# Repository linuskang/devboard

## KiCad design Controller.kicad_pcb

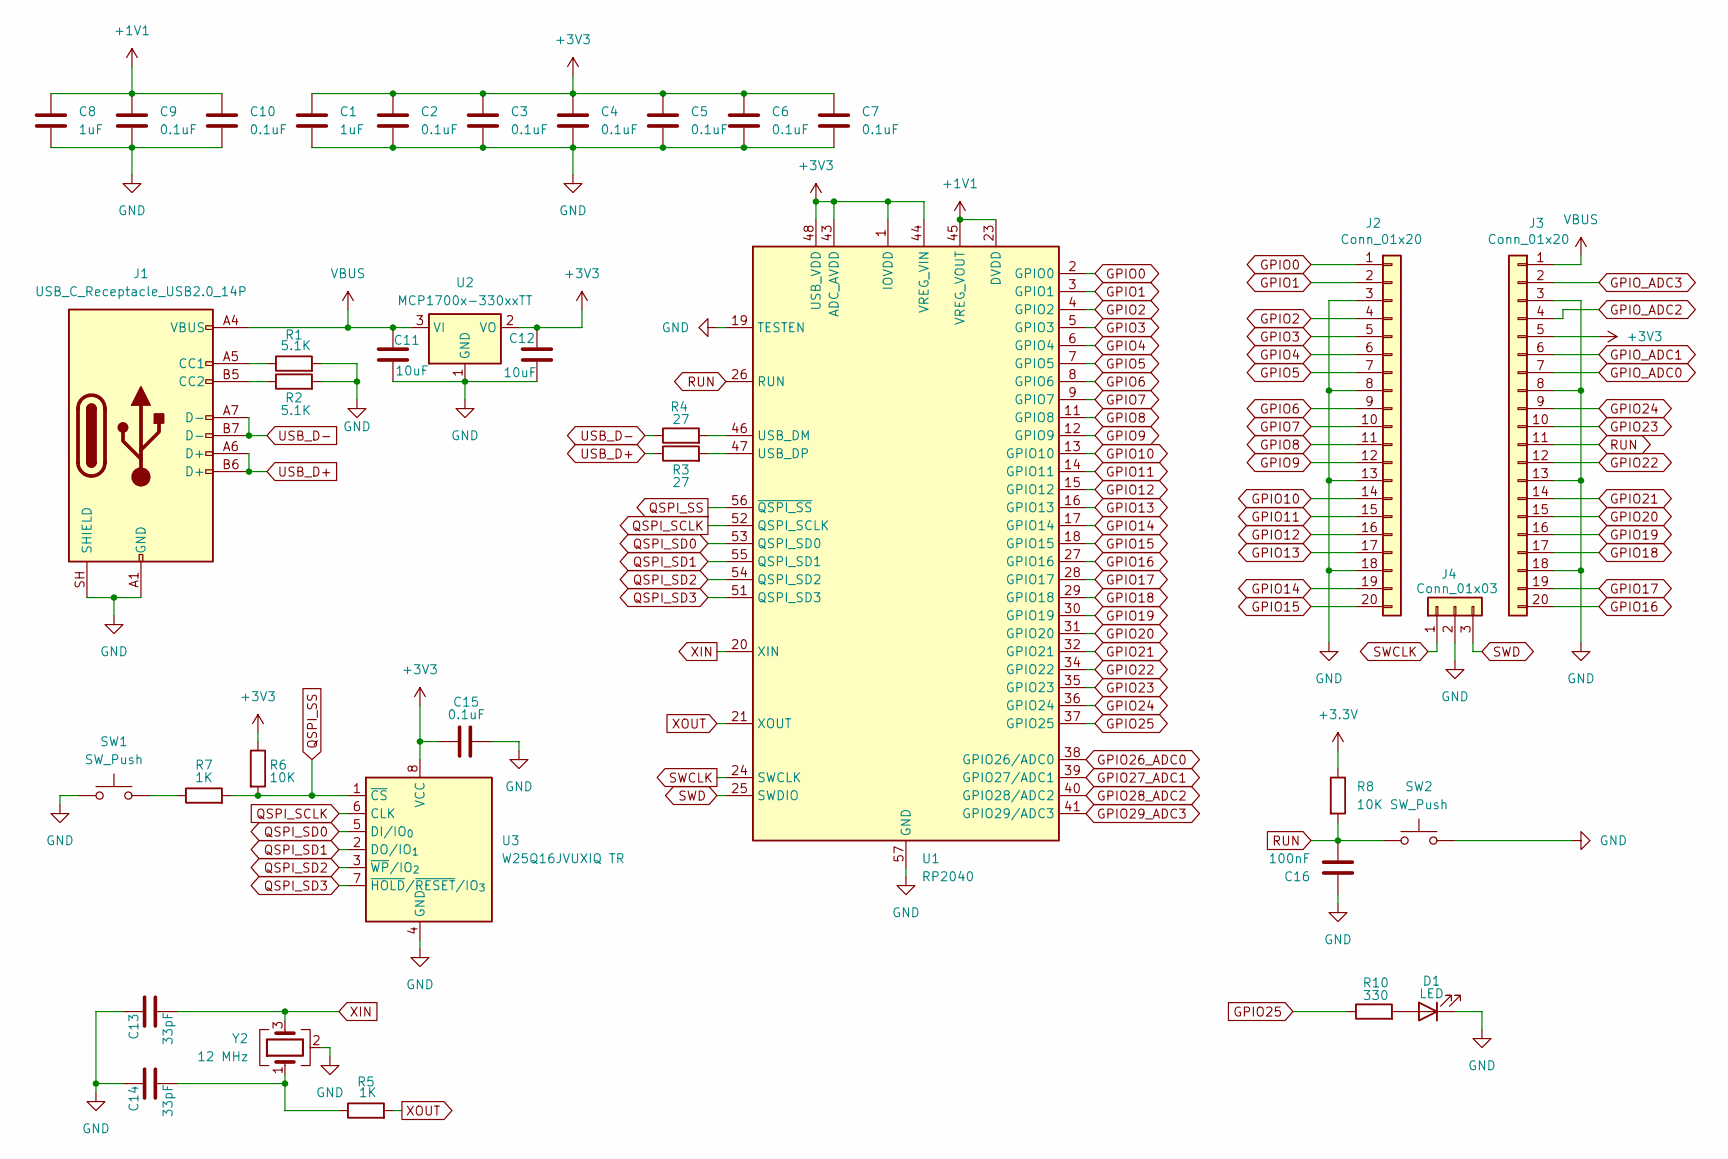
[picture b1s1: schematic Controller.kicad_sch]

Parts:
C1, C8: 1uF; C_0402_1005Metric
C2, C3, C4, C5, C6, C7, C9, C10, C15: 0.1uF; C_0402_1005Metric
C11, C12: 10uF; C_0402_1005Metric
C13, C14: 33pF; C_0402_1005Metric
C16: 100nF; C_0402_1005Metric
D1: LED; LED_0805_2012Metric_Pad1.15x1.40mm_HandSolder
J1: USB_C_Receptacle_USB2.0_14P; USB_C_Receptacle_HRO_TYPE-C-31-M-12
J2, J3: Conn_01x20; PinHeader_1x20_P2.54mm_Vertical
J4: Conn_01x03; PinHeader_1x03_P2.54mm_Vertical
R1, R2: 5.1K; R_0402_1005Metric
R3, R4: 27; R_0402_1005Metric
R5, R7: 1K; R_0402_1005Metric
R6, R8: 10K; R_0402_1005Metric
R10: 330; R_0402_1005Metric
SW1, SW2: SW_Push; SW_Push_SPST_NO_Alps_SKRK
U1: RP2040; QFN-56-1EP_7x7mm_P0.4mm_EP3.2x3.2mm
U2: MCP1700x-330xxTT; SOT-23
U3: W25Q16JVUXIQ TR; Winbond_USON-8-1EP_3x2mm_P0.5mm_EP0.2x1.6mm
Y2: 12 MHz; Crystal_SMD_3225-4Pin_3.2x2.5mm

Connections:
+1V1: C8.1, C9.1, C10.1, U1.23 (DVDD), U1.45 (VREG_VOUT), U1.50 (DVDD)
+3.3V: R8.1
+3V3: C1.1, C2.1, C3.1, C4.1, C5.1, C6.1, C7.1, C12.1, C15.2, J3.5, R6.1, U1.1 (IOVDD), U1.10 (IOVDD), U1.22 (IOVDD), U1.33 (IOVDD), U1.42 (IOVDD), U1.43 (ADC_AVDD), U1.44 (VREG_VIN), U1.48 (USB_VDD), U1.49 (IOVDD), U2.2 (VO), U3.8 (VCC)
GND: C1.2, C2.2, C3.2, C4.2, C5.2, C6.2, C7.2, C8.2, C9.2, C10.2, C11.2, C12.2, C13.1, C14.1, C15.1, C16.1, D1.1 (K), J1.A1 (GND), J1.A12 (GND), J1.B1 (GND), J1.B12 (GND), J1.SH (SHIELD), J2.3, J2.8, J2.13, J2.18, J3.3, J3.8, J3.13, J3.18, J4.2, R1.2, R2.2, SW1.1, SW2.2, U1.19 (TESTEN), U1.57 (GND), U2.1 (GND), U3.4 (GND), Y2.2 (G), Y2.4 (G)
GPIO0: J2.1, U1.2 (GPIO0)
GPIO1: J2.2, U1.3 (GPIO1)
GPIO2: J2.4, U1.4 (GPIO2)
GPIO3: J2.5, U1.5 (GPIO3)
GPIO4: J2.6, U1.6 (GPIO4)
GPIO5: J2.7, U1.7 (GPIO5)
GPIO6: J2.9, U1.8 (GPIO6)
GPIO7: J2.10, U1.9 (GPIO7)
GPIO8: J2.11, U1.11 (GPIO8)
GPIO9: J2.12, U1.12 (GPIO9)
GPIO10: J2.14, U1.13 (GPIO10)
GPIO11: J2.15, U1.14 (GPIO11)
GPIO12: J2.16, U1.15 (GPIO12)
GPIO13: J2.17, U1.16 (GPIO13)
GPIO14: J2.19, U1.17 (GPIO14)
GPIO15: J2.20, U1.18 (GPIO15)
GPIO16: J3.20, U1.27 (GPIO16)
GPIO17: J3.19, U1.28 (GPIO17)
GPIO18: J3.17, U1.29 (GPIO18)
GPIO19: J3.16, U1.30 (GPIO19)
GPIO20: J3.15, U1.31 (GPIO20)
GPIO21: J3.14, U1.32 (GPIO21)
GPIO22: J3.12, U1.34 (GPIO22)
GPIO23: J3.10, U1.35 (GPIO23)
GPIO24: J3.9, U1.36 (GPIO24)
GPIO25: R10.1, U1.37 (GPIO25)
GPIO26_ADC0: U1.38 (GPIO26/ADC0)
GPIO27_ADC1: U1.39 (GPIO27/ADC1)
GPIO28_ADC2: U1.40 (GPIO28/ADC2)
GPIO29_ADC3: U1.41 (GPIO29/ADC3)
GPIO_ADC0: J3.7
GPIO_ADC1: J3.6
GPIO_ADC2: J3.4
GPIO_ADC3: J3.2
unnamed: C14.2, R5.1, Y2.1
unnamed: D1.2 (A), R10.2
unnamed: J1.A5 (CC1), R1.1
unnamed: J1.B5 (CC2), R2.1
unnamed: R7.1, SW1.2
unnamed: R4.2, U1.46 (USB_DM)
unnamed: R3.2, U1.47 (USB_DP)
QSPI_SCLK: U1.52 (QSPI_SCLK), U3.6 (CLK)
QSPI_SD0: U1.53 (QSPI_SD0), U3.5 (DI/IO_{0})
QSPI_SD1: U1.55 (QSPI_SD1), U3.2 (DO/IO_{1})
QSPI_SD2: U1.54 (QSPI_SD2), U3.3 (~WP/IO_{2})
QSPI_SD3: U1.51 (QSPI_SD3), U3.7 (~HOLD/~RESET/IO_{3})
QSPI_SS: R6.2, R7.2, U1.56 (~QSPI_SS), U3.1 (~CS)
RUN: C16.2, J3.11, R8.2, SW2.1, U1.26 (RUN)
SWCLK: J4.1, U1.24 (SWCLK)
SWD: J4.3, U1.25 (SWDIO)
USB_D+: J1.A6 (D+), J1.B6 (D+), R3.1
USB_D-: J1.A7 (D-), J1.B7 (D-), R4.1
VBUS: C11.1, J1.A4 (VBUS), J1.A9 (VBUS), J1.B4 (VBUS), J1.B9 (VBUS), J3.1, U2.3 (VI)
XIN: C13.2, U1.20 (XIN), Y2.3
XOUT: R5.2, U1.21 (XOUT)

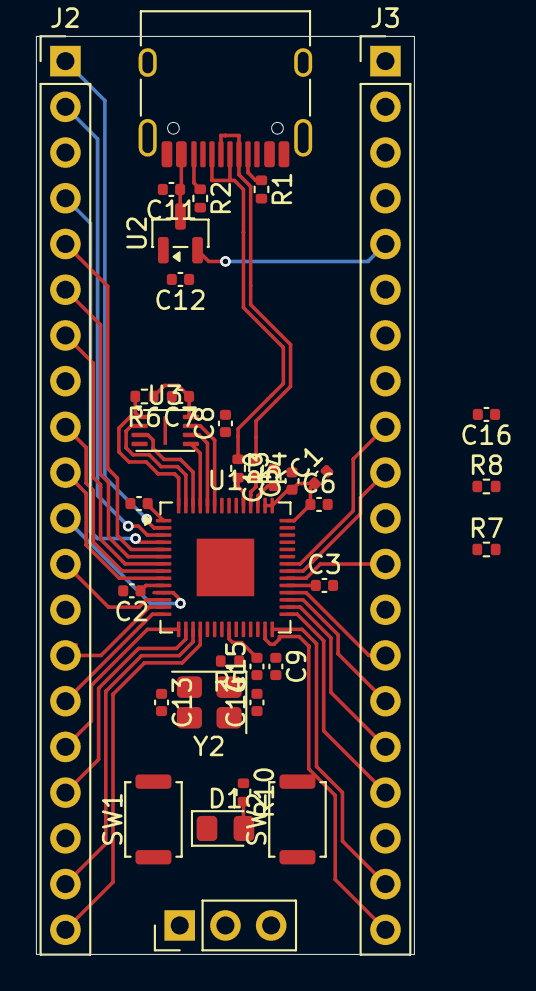
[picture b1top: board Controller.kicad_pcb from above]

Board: 2 copper layers, 21.0 x 51.0 mm, 36 parts (0 on the bottom side), 50 nets.
